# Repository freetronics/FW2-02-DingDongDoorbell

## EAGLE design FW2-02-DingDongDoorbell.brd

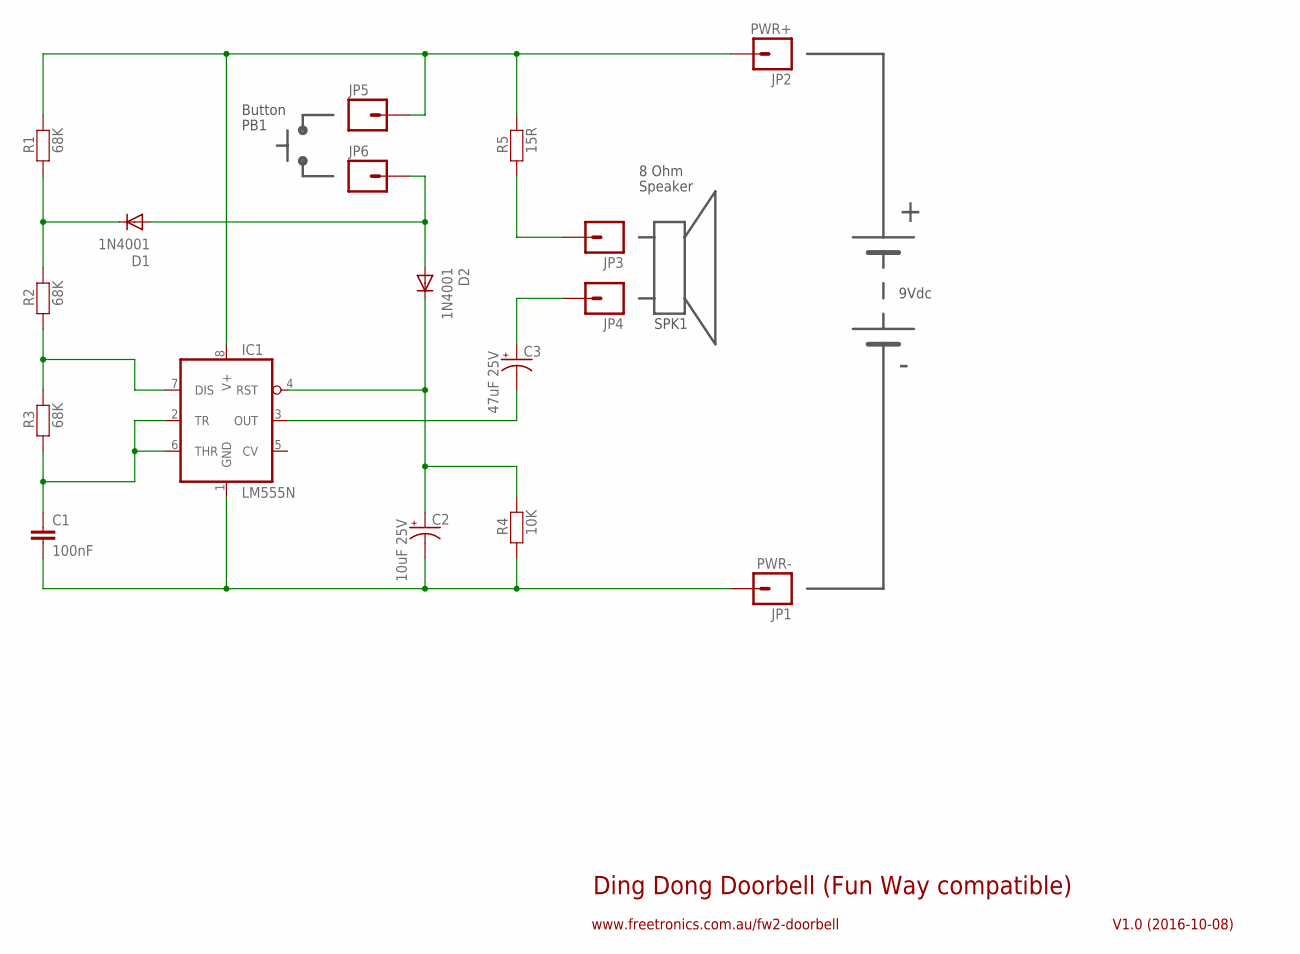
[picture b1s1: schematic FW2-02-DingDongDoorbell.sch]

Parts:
C1: 100nF; CAP-PTH-SMALL
C2: 10uF 25V; CPOL-RADIAL-10UF-25V
C3: 47uF 25V; CPOL-RADIAL-10UF-25V
D1, D2: 1N4001; DIODE-1N4001
IC1: LM555N; DIL08
JP1, JP5, JP6: PWR-; 1X01
JP2: PWR+; 1X01
JP3: SPKR+; 1X01
JP4: SPKR-; 1X01
R1, R2, R3: 68K; FREETRONICS_AXIAL-0.4
R4: 10K; FREETRONICS_AXIAL-0.4
R5: 15R; FREETRONICS_AXIAL-0.4

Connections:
unnamed: D1.C, R1.P$1 (1), R2.P$2 (2)
unnamed: IC1.7 (DIS), R2.P$1 (1), R3.P$2 (2)
unnamed: D1.A, D2.A, JP6.1
unnamed: IC1.8 (V+), JP2.1, JP5.1, R1.P$2 (2), R5.P$2 (2)
unnamed: JP3.1, R5.P$1 (1)
unnamed: C3.1 (+), JP4.1
unnamed: C3.2 (-), IC1.3 (OUT)
unnamed: C2.1 (+), D2.C, IC1.4 (RST), R4.P$2 (2)
unnamed: C1.2, C2.2 (-), IC1.1 (GND), JP1.1, R4.P$1 (1)
unnamed: C1.1, IC1.2 (TR), IC1.6 (THR), R3.P$1 (1)

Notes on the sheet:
Ding Dong Doorbell (Fun Way compatible)
V1.0 (2016-10-08)
www.freetronics.com.au/fw2-doorbell
9Vdc
8 Ohm
Speaker
Button
PB1
SPK1

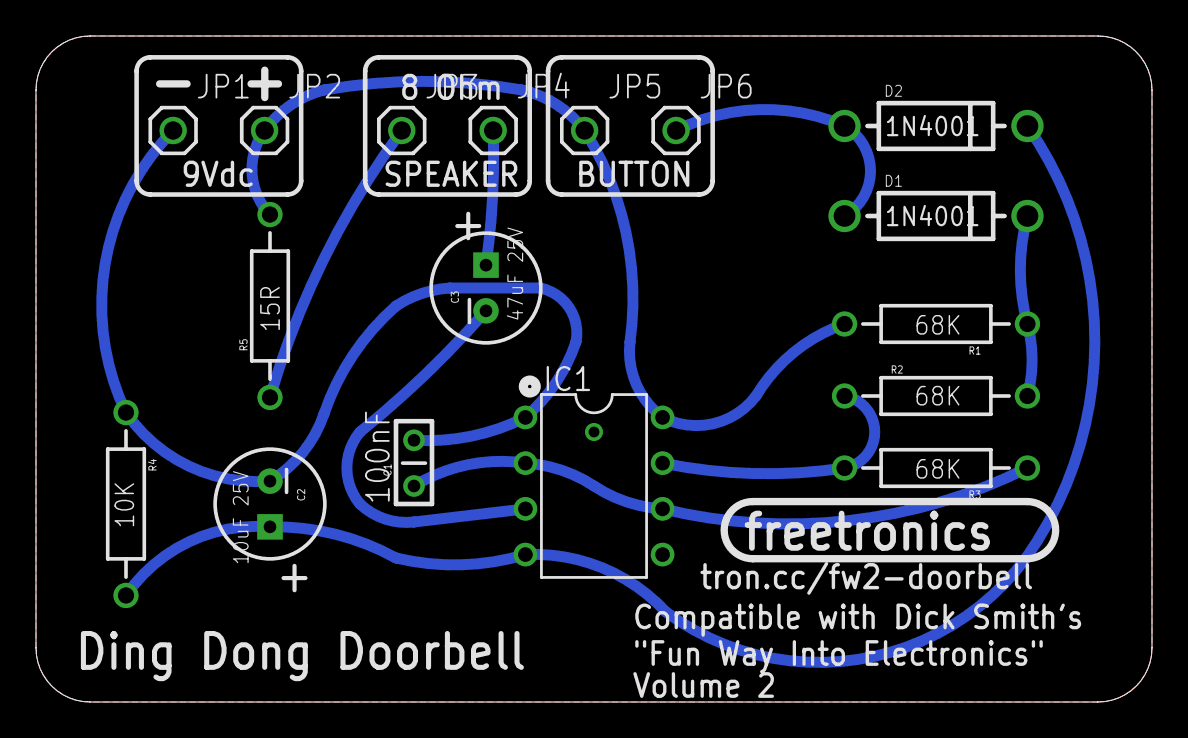
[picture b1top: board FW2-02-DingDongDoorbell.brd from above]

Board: 2 copper layers, 62.0 x 37.0 mm, 17 parts (0 on the bottom side), 10 nets.

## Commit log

2016-10-08 Initial project import
2016-10-08 Most of the schematic done, base part positions
2016-10-09 Modified 555 symbol to match original; basic PCB routing
2016-10-09 Updated silkscreen and labels
2016-10-10 Increased pad sizes; improved silkscreen

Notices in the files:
FW2-02-DingDongDoorbell.brd:
(c) 2016 Freetronics Pty Ltd
Licensed under the TAPR
Open Hardware License
